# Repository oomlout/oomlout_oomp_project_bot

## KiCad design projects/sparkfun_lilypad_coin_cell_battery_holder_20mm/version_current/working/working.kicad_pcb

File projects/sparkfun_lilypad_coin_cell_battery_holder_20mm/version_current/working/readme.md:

# LilyPad_Coin_Cell_Battery_Holder-20mm by sparkfun  
This is a harvested standardized copy of a project from github.  
The original project can be found at:  
https://github.com/sparkfun/LilyPad_Coin_Cell_Battery_Holder-20mm  
Please consult that link for additional, details, files, and license information.  
Note: It was auto harvested and if the original repo had more than one board file or anything out of the ordinary the files here are likely not representative.

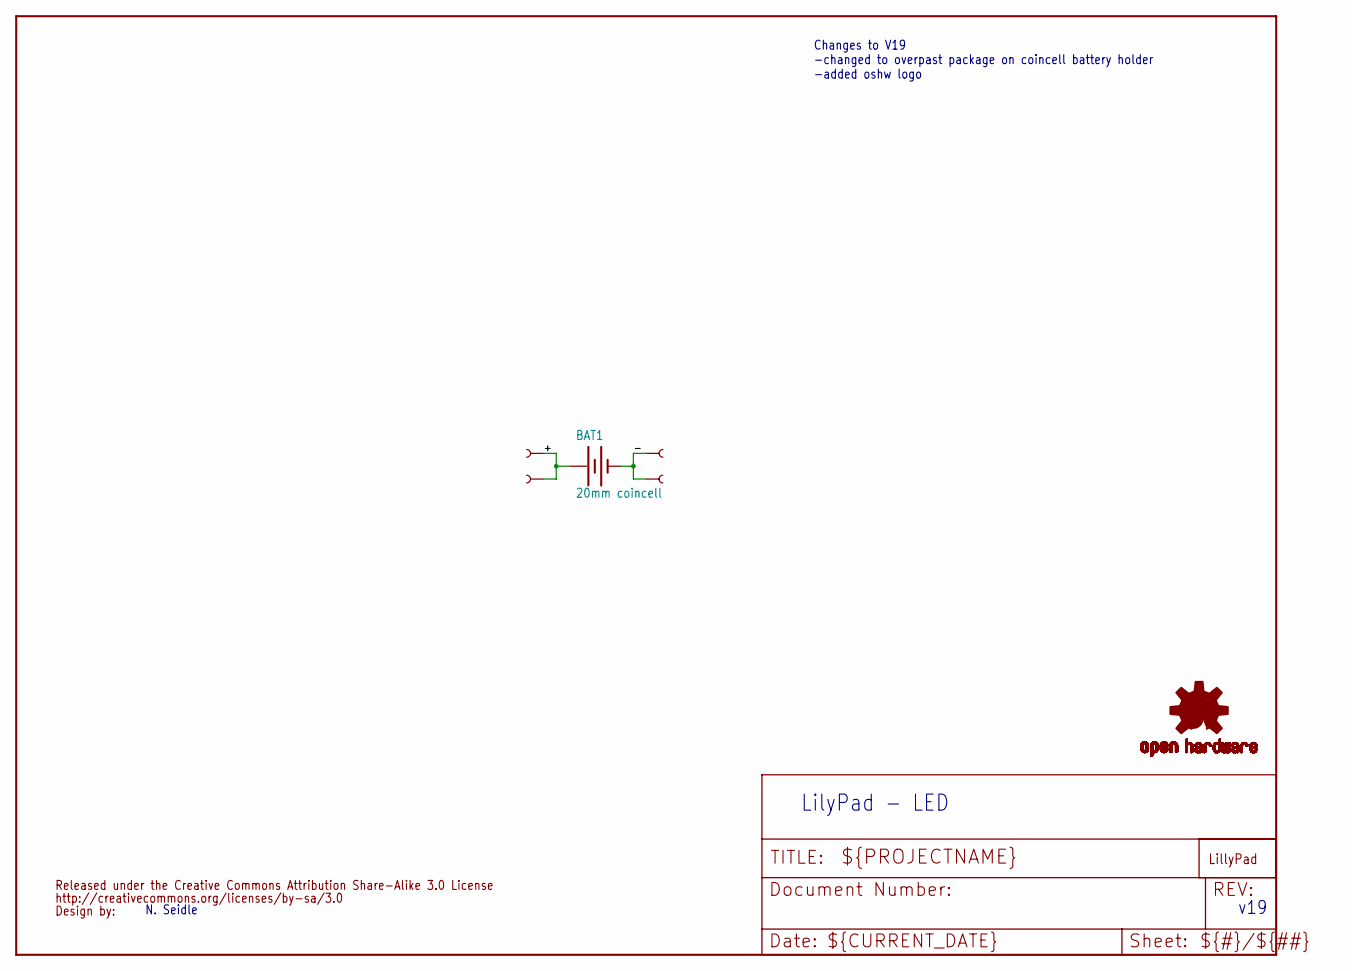
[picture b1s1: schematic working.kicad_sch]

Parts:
BAT1: 20mm coincell; BATTCON_20MM_4LEGS_OVERPASTE
U$1, U$2, U$3, U$4: SEWTAP6; PETAL-SMALL-2SIDE
U$5: LOGO-LPLP; LOGO-LILYPAD
U$6: CREATIVE_COMMONS
U$7: OSHW-LOGOS; OSHW-LOGO-S

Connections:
+: BAT1.1 (+), U$2.1, U$4.1
-: BAT1.2 (-), U$1.1, U$3.1

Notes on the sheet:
v19
Changes to V19 -changed to overpast package on coincell battery holder -added oshw logo
N. Seidle
LilyPad - LED

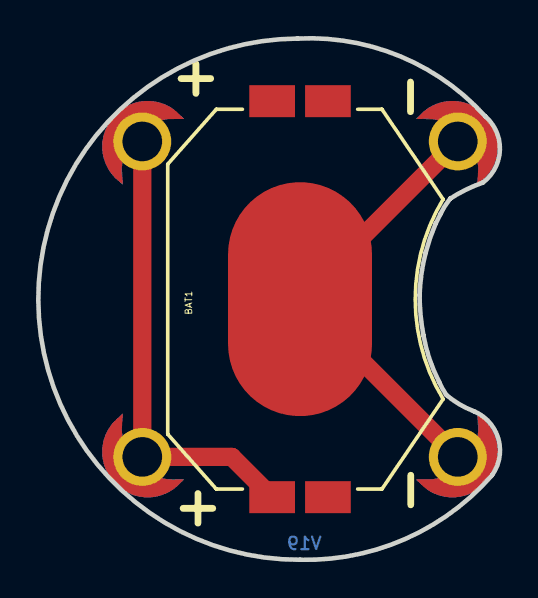
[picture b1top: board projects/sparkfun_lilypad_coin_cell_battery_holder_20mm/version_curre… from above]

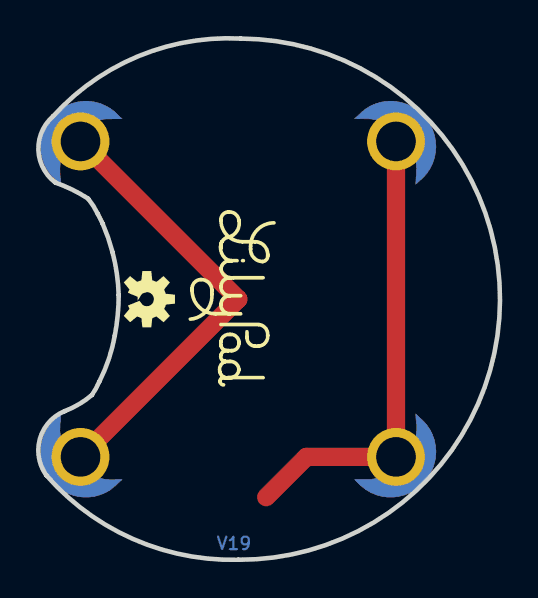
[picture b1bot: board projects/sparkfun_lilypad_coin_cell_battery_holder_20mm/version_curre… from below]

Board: 2 copper layers, 25.7 x 29.0 mm, 8 parts (2 on the bottom side), 2 nets.

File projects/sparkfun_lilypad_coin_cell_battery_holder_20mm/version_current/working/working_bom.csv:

Row,Description,Part,References,Value,Footprint,Quantity Per PCB,Status,Datasheet
1,,BATTERY20MM_4LEGS_OVERPASTE,BAT1,20mm coincell,BATTCON_20MM_4LEGS_OVERPASTE,1, ,
2,,CREATIVE_COMMONS,U$6,CREATIVE_COMMONS,CREATIVE_COMMONS,1, ,
3,,LOGO-LPLP,U$5,LOGO-LPLP,LOGO-LILYPAD,1, ,
4,,OSHW-LOGOS,U$7,OSHW-LOGOS,OSHW-LOGO-S,1, ,
5,,SEWTAP6,U$1 U$2 U$3 U$4,SEWTAP6,PETAL-SMALL-2SIDE,4, ,





Project info:
Schematic:,working
Variant:,default
Revision:,
Date:,2023-08-06_12-56-04
KiCad Version:,7.0.6-7.0.6~ubuntu22.04.1
Statistics:
Component Groups:,5
Component Count:,8 (0 SMD/ 0 THT)
Fitted Components:,8 (0 SMD/ 0 THT)
Number of PCBs:,1
Total Components:,8

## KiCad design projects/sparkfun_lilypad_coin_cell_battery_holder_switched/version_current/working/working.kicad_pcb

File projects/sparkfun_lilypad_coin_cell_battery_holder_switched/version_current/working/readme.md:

# OOMP Project  
## LilyPad_Coin_Cell_Battery_Holder-Switched  by sparkfun  
  
oomp key: oomp_projects_flat_sparkfun_lilypad_coin_cell_battery_holder_switched  
(snippet of original readme)  
  
SparkFun LilyPad Coin Cell Battery Holder-Switched  
========================================  

[*SparkFun LilyPad Coin Cell Battery Holder-Switched (DEV-11285)*](https://www.sparkfun.com/products/11285)  
  
This LilyPad Coin Cell Battery Holder has a small slide switch installed on the board,   
in-line with the power so you can shut off your project and save batteries.  
  
Repository Contents  
-------------------  
* **/Hardware** - All Eagle design files (.brd, .sch)  

License Information  
-------------------  
The hardware is released under [Creative Commons ShareAlike 4.0 International](https://creativecommons.org/licenses/by-sa/4.0/).  
Note: A portion of this sale is given back to Dr. Leah Buechley for continued development and education of e-textiles.  
  
Distributed as-is; no warranty is given.  
  
  full source readme at [readme_src.md](readme_src.md)  
  
source repo at: [https://github.com/sparkfun/LilyPad_Coin_Cell_Battery_Holder-Switched](https://github.com/sparkfun/LilyPad_Coin_Cell_Battery_Holder-Switched)  
## Board  

## Schematic  

[schematic pdf](working_schematic.pdf)  
## Images

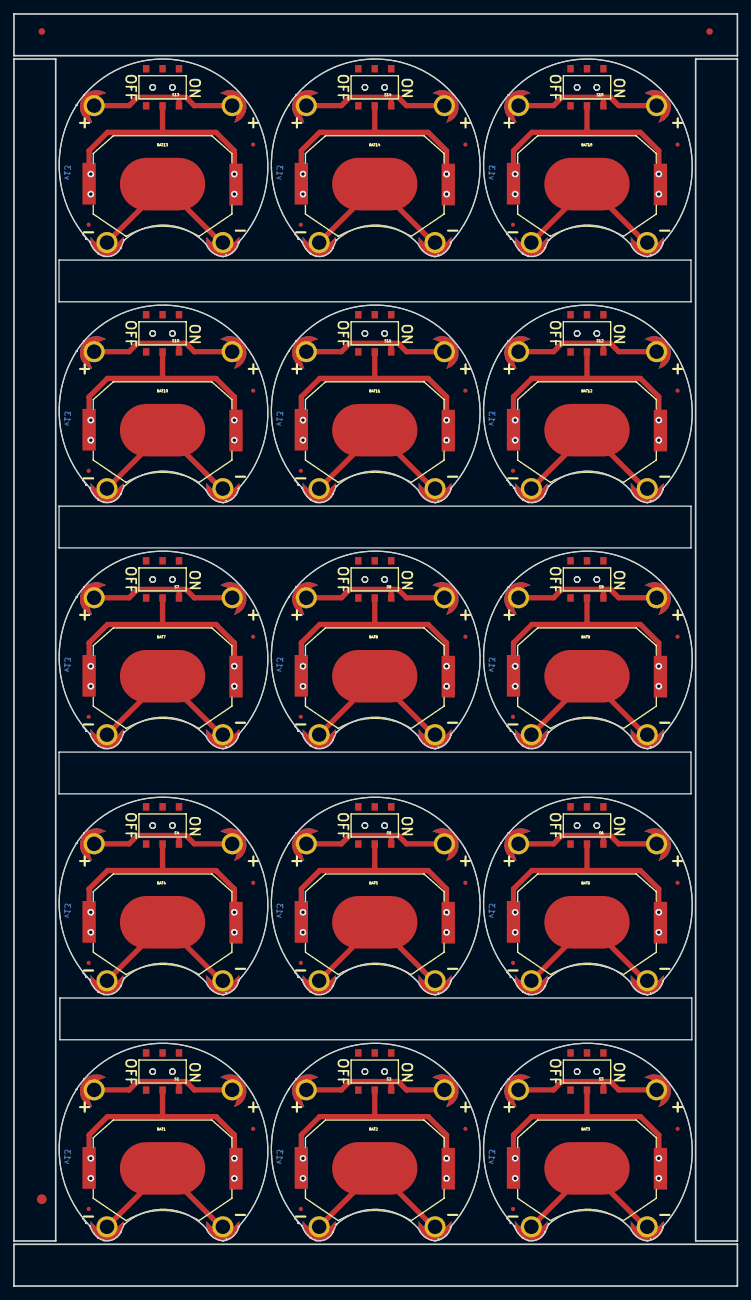
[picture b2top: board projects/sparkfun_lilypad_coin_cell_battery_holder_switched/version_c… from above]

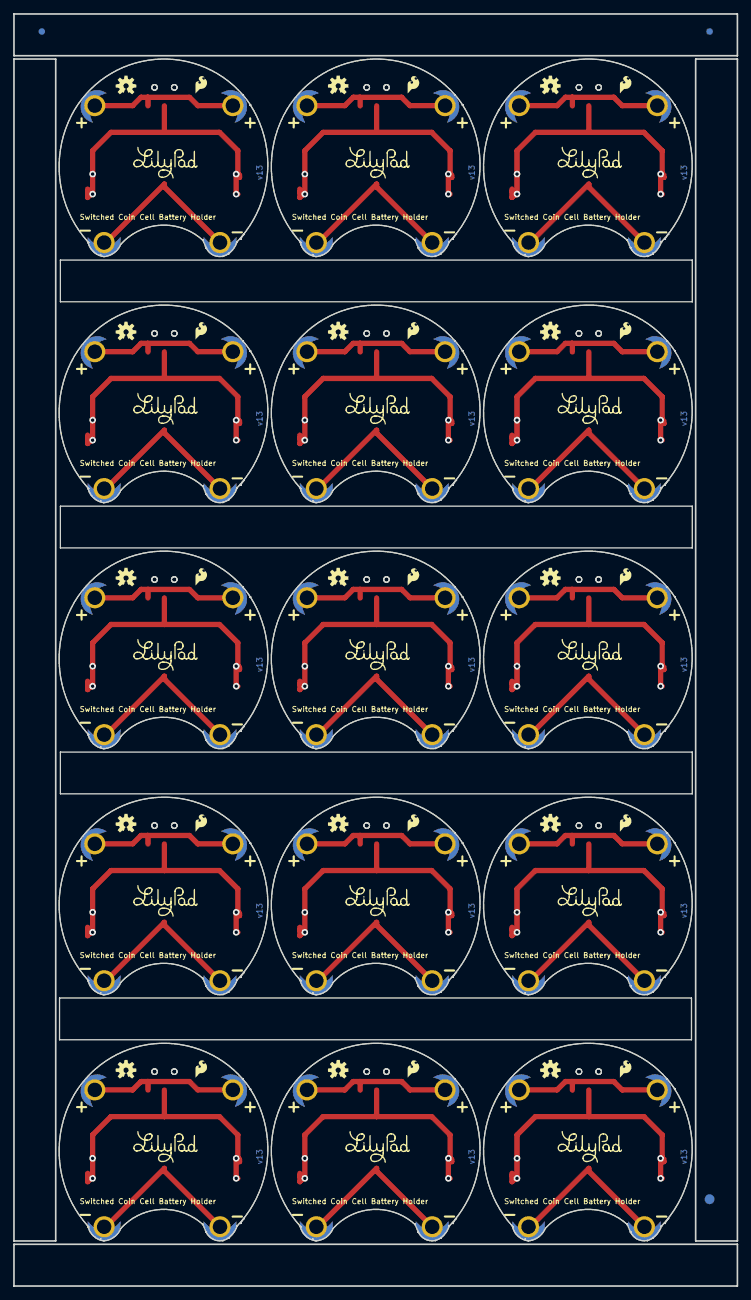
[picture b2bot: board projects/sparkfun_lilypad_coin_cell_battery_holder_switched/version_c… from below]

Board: 2 copper layers, 110.1 x 193.5 mm, 183 parts (48 on the bottom side), 45 nets.

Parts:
BAT1, BAT2, BAT3, BAT4, BAT5, BAT6, BAT7, BAT8, BAT9, BAT10, BAT11, BAT12, BAT13, BAT14, BAT15: 20mm coincell; BATTCON_20MM_4LEGS
BATB-0, BATB-1, BATB-2, BATB-3, BATB-4, BATB-5, BATB-6, BATB-7, BATB-8, BATB-9, BATB-10, BATB-11, BATB-12, BATB-13, BATB-14, BATB-15, BATB-16, BATB-17, BATB-18, BATB-19, BATB-20, BATB-21, BATB-22, BATB-23, BATB-24, BATB-25, BATB-26, BATB-27, BATB-28, BATB-29: SEWTAP6; PETAL-SMALL-2SIDE
BATT+0, BATT+1, BATT+2, BATT+3, BATT+4, BATT+5, BATT+6, BATT+7, BATT+8, BATT+9, BATT+10, BATT+11, BATT+12, BATT+13, BATT+14, BATT+15, BATT+16, BATT+17, BATT+18, BATT+19, BATT+20, BATT+21, BATT+22, BATT+23, BATT+24, BATT+25, BATT+26, BATT+27, BATT+28, BATT+29: SEWTAP6; PETAL-SMALL-2SIDE
E$1, E$2, E$3, E$4: FIDUCIAL-1X2
E$5, E$6: FIDUCIAL-1.5X3
FD1, FD2, FD3, FD4, FD5, FD6, FD7, FD8, FD9, FD10, FD11, FD12, FD13, FD14, FD15, FD16, FD17, FD18, FD19, FD20, FD21, FD22, FD23, FD24, FD25, FD26, FD27, FD28, FD29, FD30: FIDUCIALUFIDUCIAL; MICRO-FIDUCIAL
LOGO1, LOGO3, LOGO5, LOGO7, LOGO9, LOGO11, LOGO13, LOGO15, LOGO17, LOGO19, LOGO21, LOGO23, LOGO25, LOGO27, LOGO29: SFE_LOGO_FLAME.1_INCH; SFE_LOGO_FLAME_.1
LOGO2, LOGO4, LOGO6, LOGO8, LOGO10, LOGO12, LOGO14, LOGO16, LOGO18, LOGO20, LOGO22, LOGO24, LOGO26, LOGO28, LOGO30: OSHW-LOGOS; OSHW-LOGO-S
S1, S2, S3, S4, S5, S6, S7, S8, S9, S10, S11, S12, S13, S14, S15: AYZ0202
U$3, U$4, U$6, U$8, U$10, U$12, U$14, U$16, U$18, U$20, U$22, U$24, U$26, U$28, U$30: LOGO-LILYPAD
U$7, U$9, U$11, U$13, U$15, U$17, U$19, U$21, U$23, U$25, U$27, U$29: REVISION

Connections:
GND: BAT1.NEGATIVE, BATB-0.1, BATB-2.1
GND1: BAT2.NEGATIVE, BATB-1.1, BATB-3.1
GND2: BAT3.NEGATIVE, BATB-4.1, BATB-5.1
GND3: BAT4.NEGATIVE, BATB-6.1, BATB-7.1
GND4: BAT5.NEGATIVE, BATB-8.1, BATB-9.1
GND5: BAT6.NEGATIVE, BATB-10.1, BATB-11.1
GND6: BAT7.NEGATIVE, BATB-12.1, BATB-13.1
GND7: BAT8.NEGATIVE, BATB-14.1, BATB-15.1
GND8: BAT9.NEGATIVE, BATB-16.1, BATB-17.1
GND9: BAT10.NEGATIVE, BATB-18.1, BATB-19.1
GND10: BAT11.NEGATIVE, BATB-20.1, BATB-21.1
GND11: BAT12.NEGATIVE, BATB-22.1, BATB-23.1
GND12: BAT13.NEGATIVE, BATB-24.1, BATB-25.1
GND13: BAT14.NEGATIVE, BATB-26.1, BATB-27.1
GND14: BAT15.NEGATIVE, BATB-28.1, BATB-29.1
unnamed: BAT1.POSITIVE@1, BAT1.POSITIVE@2, BAT1.POSITIVE@3, BAT1.POSITIVE@4, S1.2
unnamed: BATT+0.1, BATT+2.1, S1.1
unnamed: BAT2.POSITIVE@1, BAT2.POSITIVE@2, BAT2.POSITIVE@3, BAT2.POSITIVE@4, S2.2
unnamed: BATT+1.1, BATT+3.1, S2.1
unnamed: BAT3.POSITIVE@1, BAT3.POSITIVE@2, BAT3.POSITIVE@3, BAT3.POSITIVE@4, S3.2
unnamed: BATT+4.1, BATT+5.1, S3.1
unnamed: BAT4.POSITIVE@1, BAT4.POSITIVE@2, BAT4.POSITIVE@3, BAT4.POSITIVE@4, S4.2
unnamed: BATT+6.1, BATT+7.1, S4.1
unnamed: BAT5.POSITIVE@1, BAT5.POSITIVE@2, BAT5.POSITIVE@3, BAT5.POSITIVE@4, S5.2
unnamed: BATT+8.1, BATT+9.1, S5.1
unnamed: BAT6.POSITIVE@1, BAT6.POSITIVE@2, BAT6.POSITIVE@3, BAT6.POSITIVE@4, S6.2
unnamed: BATT+10.1, BATT+11.1, S6.1
unnamed: BAT7.POSITIVE@1, BAT7.POSITIVE@2, BAT7.POSITIVE@3, BAT7.POSITIVE@4, S7.2
unnamed: BATT+12.1, BATT+13.1, S7.1
unnamed: BAT8.POSITIVE@1, BAT8.POSITIVE@2, BAT8.POSITIVE@3, BAT8.POSITIVE@4, S8.2
unnamed: BATT+14.1, BATT+15.1, S8.1
unnamed: BAT9.POSITIVE@1, BAT9.POSITIVE@2, BAT9.POSITIVE@3, BAT9.POSITIVE@4, S9.2
unnamed: BATT+16.1, BATT+17.1, S9.1
unnamed: BAT10.POSITIVE@1, BAT10.POSITIVE@2, BAT10.POSITIVE@3, BAT10.POSITIVE@4, S10.2
unnamed: BATT+18.1, BATT+19.1, S10.1
unnamed: BAT11.POSITIVE@1, BAT11.POSITIVE@2, BAT11.POSITIVE@3, BAT11.POSITIVE@4, S11.2
unnamed: BATT+20.1, BATT+21.1, S11.1
unnamed: BAT12.POSITIVE@1, BAT12.POSITIVE@2, BAT12.POSITIVE@3, BAT12.POSITIVE@4, S12.2
unnamed: BATT+22.1, BATT+23.1, S12.1
unnamed: BAT13.POSITIVE@1, BAT13.POSITIVE@2, BAT13.POSITIVE@3, BAT13.POSITIVE@4, S13.2
unnamed: BATT+24.1, BATT+25.1, S13.1
unnamed: BAT14.POSITIVE@1, BAT14.POSITIVE@2, BAT14.POSITIVE@3, BAT14.POSITIVE@4, S14.2
unnamed: BATT+26.1, BATT+27.1, S14.1
unnamed: BAT15.POSITIVE@1, BAT15.POSITIVE@2, BAT15.POSITIVE@3, BAT15.POSITIVE@4, S15.2
unnamed: BATT+28.1, BATT+29.1, S15.1

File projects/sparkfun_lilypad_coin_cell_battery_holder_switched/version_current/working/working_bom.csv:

"Id";"Designator";"Footprint";"Quantity";"Designation";"Supplier and ref";
1;"BATB-21,BATB-23,BATT+8,BATT+29,BATB-1,BATT+19,BATB-22,BATB-25,BATT+15,BATB-9,BATT+27,BATT+21,BATB-14,BATB-8,BATT+16,BATT+26,BATT+28,BATT+20,BATB-28,BATB-4,BATT+11,BATT+13,BATB-3,BATB-0,BATB-27,BATB-24,BATT+0,BATB-7,BATT+9,BATT+12,BATT+7,BATB-15,BATB-16,BATB-13,BATB-11,BATT+6,BATT+24,BATB-5,BATB-17,BATT+5,BATT+23,BATT+18,BATT+1,BATT+14,BATT+3,BATT+17,BATT+2,BATB-29,BATT+25,BATB-12,BATT+4,BATT+22,BATT+10,BATB-18,BATB-19,BATB-20,BATB-10,BATB-2,BATB-26,BATB-6";"PETAL-SMALL-2SIDE";60;"SEWTAP6";;;
2;"FD30,FD25,FD12,FD24,FD20,FD15,FD19,FD10,FD5,FD7,FD1,FD22,FD18,FD17,FD6,FD4,FD21,FD11,FD3,FD13,FD23,FD27,FD29,FD28,FD16,FD26,FD2,FD14,FD9,FD8";"MICRO-FIDUCIAL";30;"FIDUCIALUFIDUCIAL";;;
3;"U$17,U$11,U$13,U$21,U$15,U$9,U$27,U$7,U$19,U$25,U$29,U$23";"REVISION";12;"REVISION";;;
4;"S3,S12,S15,S5,S11,S4,S7,S6,S1,S8,S10,S14,S2,S9,S13";"AYZ0202";15;"";;;
5;"BAT5,BAT4,BAT9,BAT8,BAT2,BAT12,BAT6,BAT15,BAT14,BAT10,BAT11,BAT3,BAT7,BAT1,BAT13";"BATTCON_20MM_4LEGS";15;"20mm coincell";;;
6;"E$3,E$1,E$2,E$4";"FIDUCIAL-1X2";4;"";;;
7;"E$5,E$6";"FIDUCIAL-1.5X3";2;"";;;
8;"LOGO21,LOGO13,LOGO23,LOGO17,LOGO11,LOGO3,LOGO25,LOGO7,LOGO5,LOGO29,LOGO27,LOGO9,LOGO1,LOGO15,LOGO19";"SFE_LOGO_FLAME_.1";15;"SFE_LOGO_FLAME.1_INCH";;;
9;"LOGO14,LOGO16,LOGO8,LOGO20,LOGO26,LOGO6,LOGO10,LOGO24,LOGO30,LOGO22,LOGO18,LOGO12,LOGO2,LOGO28,LOGO4";"OSHW-LOGO-S";15;"OSHW-LOGOS";;;
10;"U$22,U$30,U$18,U$20,U$24,U$16,U$8,U$4,U$3,U$10,U$14,U$6,U$26,U$28,U$12";"LOGO-LILYPAD";15;"";;;

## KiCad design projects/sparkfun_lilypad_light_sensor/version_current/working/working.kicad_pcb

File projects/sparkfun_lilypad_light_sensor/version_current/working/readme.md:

# OOMP Project  
## LilyPad_Light_Sensor  by sparkfun  
  
oomp key: oomp_projects_flat_sparkfun_lilypad_light_sensor  
(snippet of original readme)  
  
LilyPad Light Sensor  
========================================  

[*LilyPad Light Sensor(DEV-08464)*](https://www.sparkfun.com/products/8464)  
  
This is a simple to use light sensor that outputs an analog value from 0 to 5V.   
With exposure to daylight, this sensor will output 5V.   
Covering the sensor with your hand, the sensor will output 0V.   
In a normal indoor lighting situation, the sensor will output from 1 to 2V.  
  
Repository Contents  
-------------------  
* **/Firmware** - Arduino Example Code  
* **/Hardware** - Eagle design files (.brd, .sch)  
* **/Production** - Production panel files (.brd)  
  
Documentation  
--------------  
* **[Hookup Guide](https://learn.sparkfun.com/tutorials/lilypad-light-sensor-hookup-guide)** - Basic hookup guide for the LilyPad Light Sensor.  
* **[SparkFun Fritzing repo](https://github.com/sparkfun/Fritzing_Parts)** - Fritzing diagrams for SparkFun products.  
* **[SparkFun 3D Model repo](https://github.com/sparkfun/3D_Models)** - 3D models of SparkFun products.   

License Information  
-------------------  
This product is _**open source**_!   
  
The **hardware** is released under [Creative Commons ShareAlike 4.0 International](https://creativecommons.org/licenses/by-sa/4.0/).  
  
Please use, reuse, and modify these files as you see fit. Please maintain attribution to SparkFun Electronics and release anything derivative under the same license.  
  
Distributed as-is; no warranty is given.  
  full source readme at [readme_src.md](readme_src.md)  
  
source repo at: [https://github.com/sparkfun/LilyPad_Light_Sensor](https://github.com/sparkfun/LilyPad_Light_Sensor)  
## Board  

## Schematic  

[schematic pdf](working_schematic.pdf)  
## Images

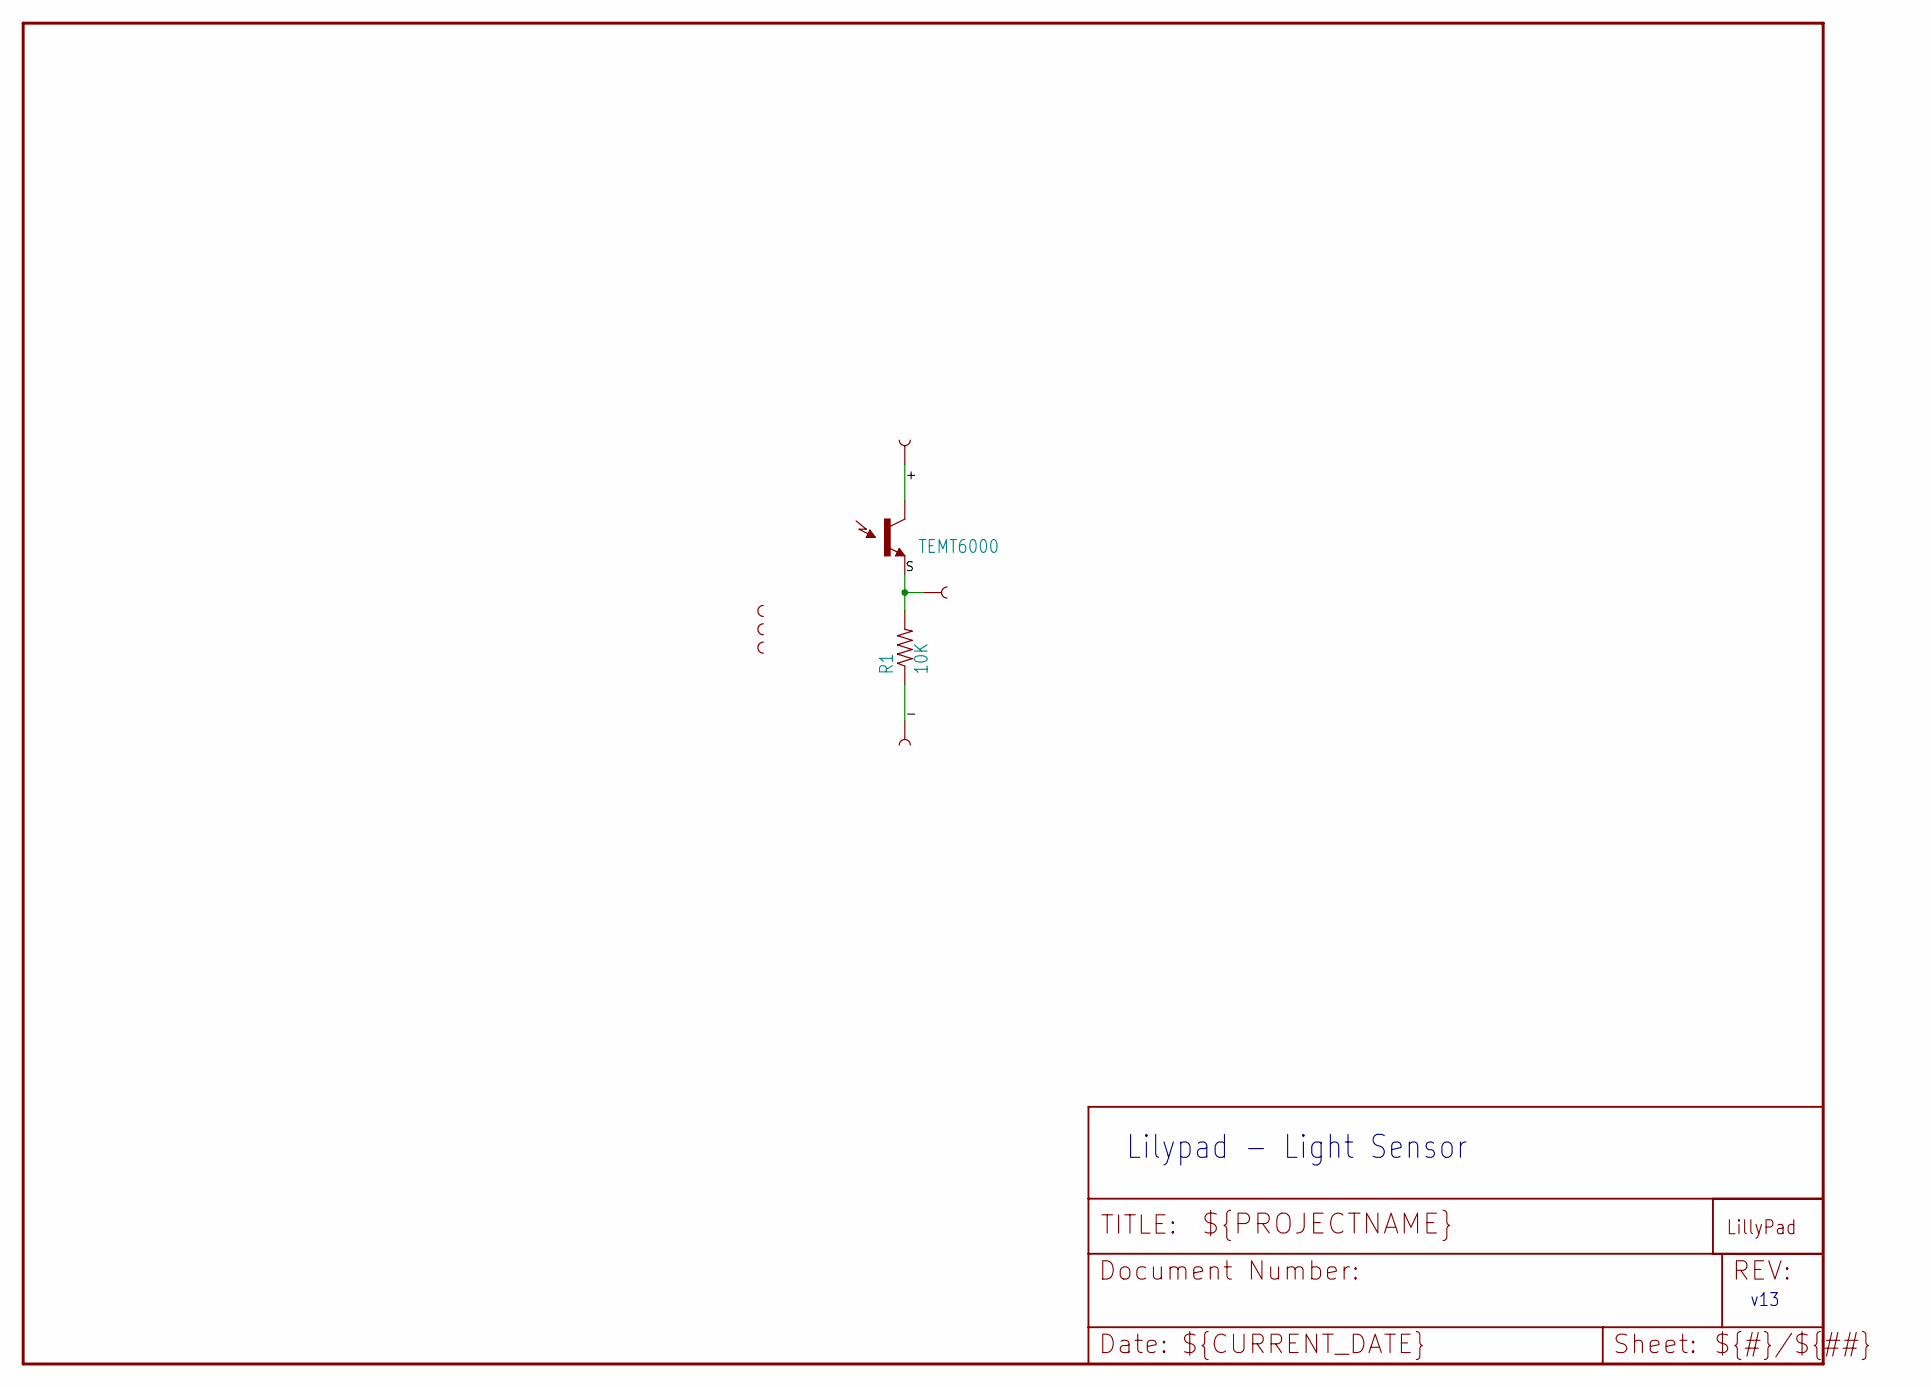
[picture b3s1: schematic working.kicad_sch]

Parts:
LIGHT1, LIGHT2, LIGHT3: SEWTAP-NOHOLE2; PETAL-NOHOLE-2SIDE
LIGHT+0: SEWTAP6; PETAL-SMALL-2SIDE
LIGHT-0: SEWTAP6; PETAL-SMALL-2SIDE
LIGHTS0: SEWTAP6; PETAL-SMALL-2SIDE
R1: 10K; C0402
U1: TEMT6000; TEMT6000-SEN
U$2: LOGO-LPLP; LOGO-LILYPAD

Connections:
+: LIGHT+0.1, U1.COLLECTOR (C1)
-: LIGHT-0.1, R1.1
S: LIGHTS0.1, R1.2, U1.EMITTER (E1)

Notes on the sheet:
v13
Lilypad - Light Sensor

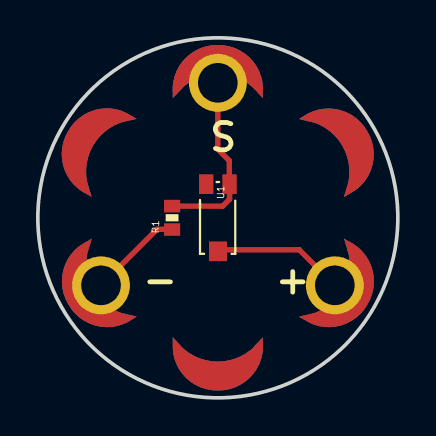
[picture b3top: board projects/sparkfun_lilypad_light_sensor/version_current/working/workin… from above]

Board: 2 copper layers, 20.0 x 20.0 mm, 9 parts (1 on the bottom side), 3 nets.

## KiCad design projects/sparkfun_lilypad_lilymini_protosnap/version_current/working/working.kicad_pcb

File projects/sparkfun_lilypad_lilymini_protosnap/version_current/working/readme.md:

# LilyPad_LilyMini_ProtoSnap by sparkfun  
This is a harvested standardized copy of a project from github.  
The original project can be found at:  
https://github.com/sparkfun/LilyPad_LilyMini_ProtoSnap  
Please consult that link for additional, details, files, and license information.  
Note: It was auto harvested and if the original repo had more than one board file or anything out of the ordinary the files here are likely not representative.

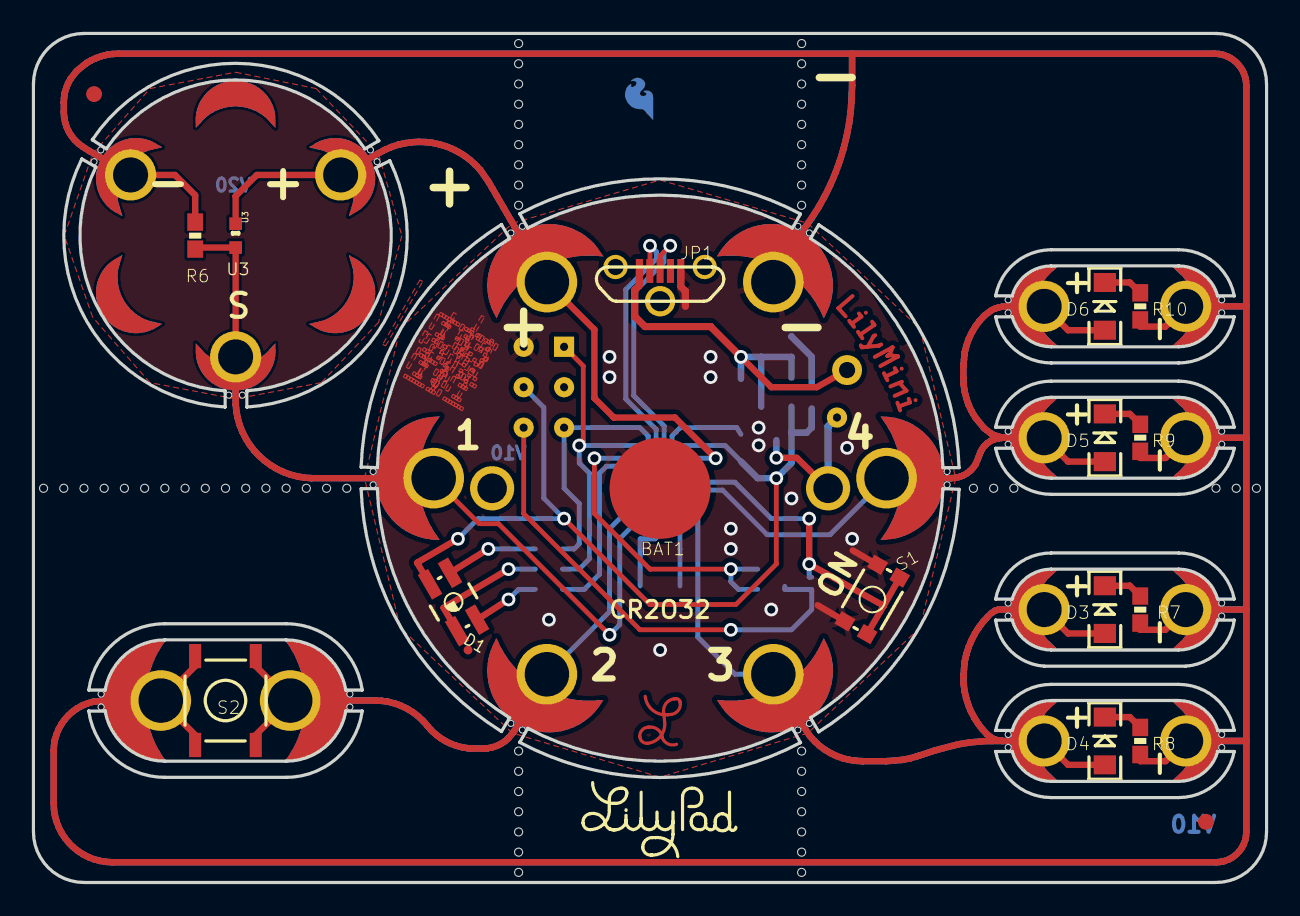
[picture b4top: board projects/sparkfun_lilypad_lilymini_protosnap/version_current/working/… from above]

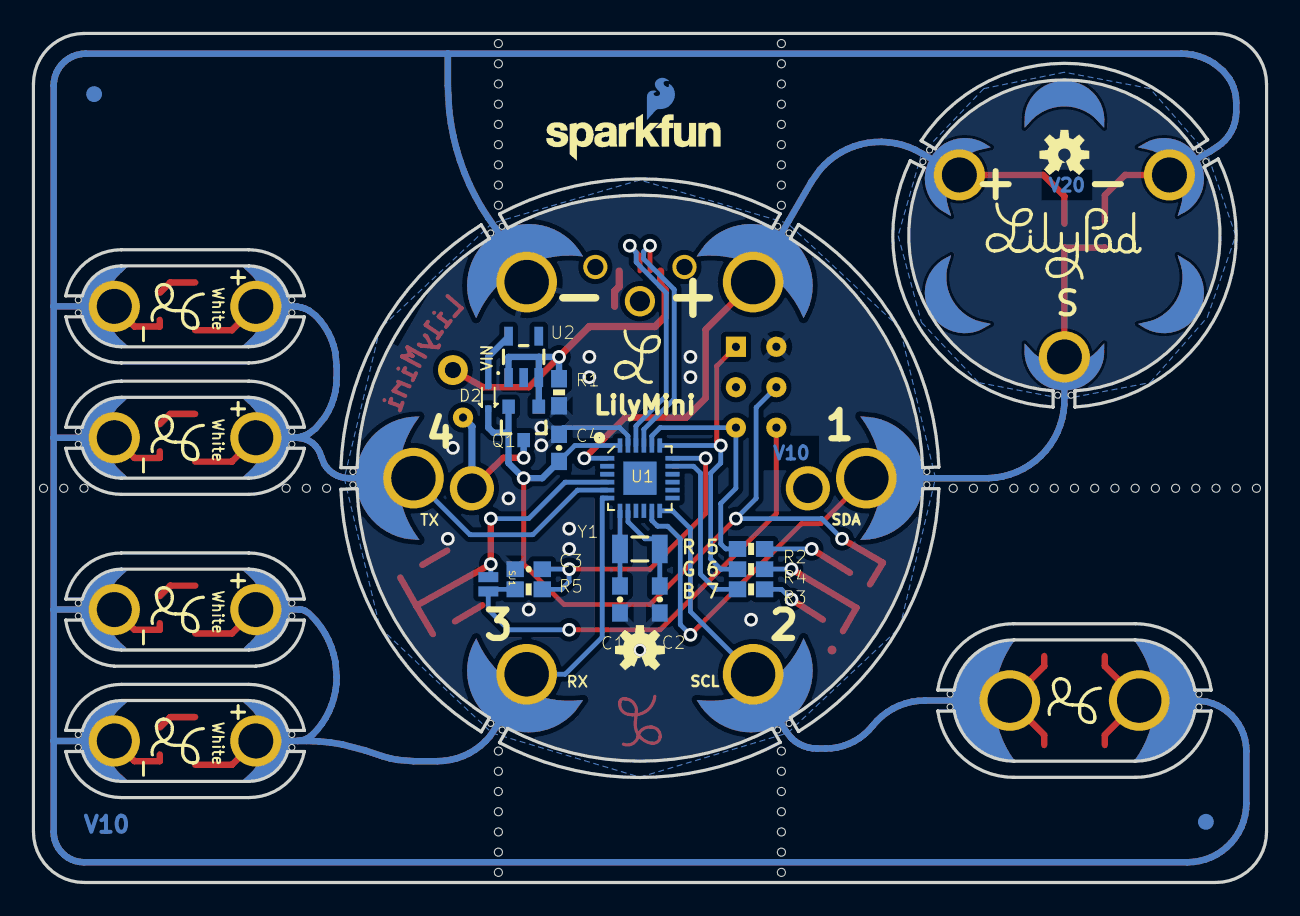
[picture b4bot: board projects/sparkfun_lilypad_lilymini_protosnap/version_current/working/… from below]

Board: 2 copper layers, 77.5 x 53.3 mm, 170 parts (35 on the bottom side), 27 nets.

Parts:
$1_61_$_2016-09-25_21-56-09: OSHW-LOGOS; OSHW-LOGO-S
@HOLE0, @HOLE1, @HOLE2, @HOLE3, @HOLE4, @HOLE5, @HOLE6, @HOLE7, @HOLE8, @HOLE9, @HOLE10, @HOLE11, @HOLE12, @HOLE13, @HOLE14, @HOLE15, @HOLE16, @HOLE17, @HOLE18, @HOLE19, @HOLE20, @HOLE21, @HOLE22, @HOLE23, @HOLE24, @HOLE25, @HOLE26, @HOLE27, @HOLE28, @HOLE29, @HOLE30, @HOLE31, @HOLE32, @HOLE33, @HOLE34, @HOLE35, @HOLE36, @HOLE37, @HOLE38, @HOLE39, @HOLE40, @HOLE41, @HOLE42, @HOLE43, @HOLE44, @HOLE45, @HOLE46, @HOLE47, @HOLE48, @HOLE49, @HOLE50, @HOLE51, @HOLE52, @HOLE53, @HOLE54, @HOLE55, @HOLE56, @HOLE57, @HOLE58, @HOLE59, @HOLE60, @HOLE61, @HOLE62, @HOLE63, @HOLE64, @HOLE65, @HOLE66, @HOLE67, @HOLE68, @HOLE69, @HOLE70, @HOLE71, @HOLE72, @HOLE73, @HOLE74, @HOLE75, @HOLE76, @HOLE77, @HOLE78, @HOLE79, @HOLE80, @HOLE81, @HOLE82, @HOLE83, @HOLE84, @HOLE85, @HOLE86, @HOLE87, @HOLE88, @HOLE89, @HOLE90, @HOLE91: (no value)
BAT1: CR2032; BATTERY_20MM_PTH_KIT
C1, C2: 15pF; 0603-CAP
C3, C4: 0.1uF; 0603-CAP
D1: P-LCC-4-3
D2: RB751; SOD-523
D3, D4, D5, D6: LED-1206
FD1, FD2, FD3, FD4: FIDUCIAL1X2; FIDUCIAL-1X2
FRAME1: FRAME-LETTER; CREATIVE_COMMONS
JP1: USB-B-MICRO-SMD_VERT
JP2: 1X01NS
JP3: 1X01_POGOPIN_PAD_NOSILK_1SIDE_SQUARE
JP4, JP5, JP6, JP7, JP8, JP9: 1X01_POGOPIN_PAD_NOSILK_1SIDE_ROUND
JP12, JP13: PETAL-MEDIUM-2SIDE
JP20, JP21, JP22, JP23, JP24, JP25, JP26, JP27: PETAL-SMALL-2SIDE
LOGO1: LOGO-L
LOGO2: LOGO-L-TOP
LOGO3: OSHW-LOGOS; OSHW-LOGO-S
LOGO4: SFE_LOGO_NAME.1_INCH; SFE_LOGO_NAME_.1
Q1: ZXMP6A13F; SOT23-3
R1, R6: 10K; 0603-RES
R2, R5: 330; 0603-RES
R3: 2K; 0603-RES
R4: 1K; 0603-RES
R7, R8, R9, R10: 150; 0603-RES
S1: TACTILE_SWITCH_SMD_4.6X2.8MM
S2: TACTILE-SWITCH-SMD
SEWTAP1, SEWTAP2, SEWTAP3, SEWTAP4: PETAL-MEDIUM-2SIDE
SEWTAP+0: PETAL-MEDIUM-2SIDE
SEWTAP-0: PETAL-MEDIUM-2SIDE
SEWTAPLS+0: PLUS; PETAL-SMALL-2SIDE
SEWTAPLS-0: MINUS; PETAL-SMALL-2SIDE
SEWTAPLSOUT0: OUT; PETAL-SMALL-2SIDE
SJ1: PAD-JUMPER-2-NO_NO_SILK
ST1, ST2, ST3: PETAL-NOHOLE-2SIDE
U1: SAMD11D14A-M; QFN-24_ALT2
U2: AP2112K-3.3V; SOT23-5
U3: ALS-PT19
U$1: LOGO-LILYPAD
U$2: LOGO-LPLP; LOGO-LILYPAD
U$4: SFE_LOGO_FLAME_COPPER_EXPOSED_.1
U$5, U$6, U$7, U$8, U$9: LOGO-L
Y1: 32.768kHz; CRYSTAL-SMD-3.2X1.5MM

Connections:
B: D1.3, R2.2
BATT3V: BAT1.+1, BAT1.+2, JP9.P$1, Q1.3
BUTTON: S1.1, S1.2, SJ1.1, U1.4
G: D1.2, R3.2
GND: BAT1.-3, C1.1, C2.1, C3.2, C4.2, JP1.GND, JP4.P$1, JP13.1, JP21.1, JP23.1, JP25.1, JP27.1, R1.1, R6.1, R7.1, R8.1, R9.1, R10.1, S1.3, S1.4, S2.3, S2.4, SEWTAP-0.1, SEWTAPLS-0.1, U1.23, U2.2
unnamed: D2.A, U2.5
unnamed: D3.C, R7.2
unnamed: D4.C, R8.2
unnamed: D5.C, R9.2
unnamed: D6.C, R10.2
R: D1.1, R4.2
SEWTAP1: R6.2, SEWTAP1.1, SEWTAPLSOUT0.1, U1.11, U3.E
SEWTAP2: JP12.1, S2.1, S2.2, SEWTAP2.1, U1.12
SEWTAP3: D3.A, D4.A, JP20.1, JP22.1, SEWTAP3.1, U1.6
SEWTAP4: D5.A, D6.A, JP24.1, JP26.1, SEWTAP4.1, U1.5
SEWTAP+: SEWTAP+0.1, SEWTAPLS+0.1, U1.1, U3.C
USB5V: JP1.VBUS, JP2.1, Q1.1, R1.2, U2.1, U2.3
USB_N: JP1.D-, U1.21
USB_P: JP1.D+, U1.22
VDD: C4.1, D1.4, D2.C, JP6.P$1, Q1.2, U1.24
X1: C1.2, U1.7, Y1.P$2
X2: C2.2, U1.8, Y1.P$1
~BLUE/SWDIO: JP7.P$1, R2.1, U1.20
~GREEN: R3.1, U1.17
~RED/SWDCLK: JP3.P$1, R4.1, U1.19
~RST: JP8.P$1, R5.2, SJ1.2
~RST1: C3.1, R5.1, U1.18

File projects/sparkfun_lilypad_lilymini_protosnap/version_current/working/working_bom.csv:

Row,Description,Part,References,Value,Footprint,Quantity Per PCB,Status,Datasheet
1,,OSHW-LOGOS,$1_61_$_2016-09-25_21-56-09,OSHW-LOGOS,OSHW-LOGO-S,1, ,
2,,BATTERY20MM_PTH_KIT,BAT1,CR2032,BATTERY_20MM_PTH_KIT,1, ,
3,,15PF-50V-5%(0603),C1 C2,15pF,0603-CAP,2, ,
4,,0.1UF-25V(+80/-20%)(0603),C3 C4,0.1uF,0603-CAP,2, ,
5,,0.13_RGB_LEDPLCC,D1,0.13_RGB_LEDPLCC,P-LCC-4-3,1, ,
6,,DIODE-SCHOTTKY-RB751,D2,DIODE-SCHOTTKY-RB751,SOD-523,1, ,
7,,LED-WHITE1206,D3 D4 D5 D6,LED-WHITE1206,LED-1206,4, ,
8,,FRAME-LETTER,FRAME1,FRAME-LETTER,CREATIVE_COMMONS,1, ,
9,,SparkFun-Connectors_M01SMDNS,JP2,M01SMDNS,1X01NS,1, ,
10,,M01_POGOPAD_20M_NS_1S_ROUND,JP4 JP5 JP6 JP7 JP8 JP9,M01_POGOPAD_20M_NS_1S_ROUND,1X01_POGOPIN_PAD_NOSILK_1SIDE_ROUND,6, ,
11,,M01_POGOPAD_20M_NS_1S_SQUARE,JP3,M01_POGOPAD_20M_NS_1S_SQUARE,1X01_POGOPIN_PAD_NOSILK_1SIDE_SQUARE,1, ,
12,,SEWTAP6,JP20 JP21 JP22 JP23 JP24 JP25 JP26 JP27 SEWTAPLS+0 SEWTAPLS-0 SEWTAPLSOUT0,SEWTAP6,PETAL-SMALL-2SIDE,11, ,
13,,SEWTAP8,JP12 JP13 SEWTAP1 SEWTAP2 SEWTAP3 SEWTAP4 SEWTAP+0 SEWTAP-0,SEWTAP8,PETAL-MEDIUM-2SIDE,8, ,
14,,USB_MICROB_PLUGUSB-B-MICRO-SMD-VERT,JP1,USB_MICROB_PLUGUSB-B-MICRO-SMD-VERT,USB-B-MICRO-SMD_VERT,1, ,
15,,LILYLOGO-L-TOP,LOGO2,LILYLOGO-L-TOP,LOGO-L-TOP,1, ,
16,,LOGO-LPL,LOGO1,LOGO-LPL,LOGO-L,1, ,
17,,SFE_LOGO_NAME.1_INCH,LOGO4,SFE_LOGO_NAME.1_INCH,SFE_LOGO_NAME_.1,1, ,
18,,MOSFET-PCHANNEL,Q1,MOSFET-PCHANNEL,SOT23-3,1, ,
19,,RESISTOR0603,R7 R8 R9 R10,150,0603-RES,4, ,
20,,330OHM1/10W1%(0603),R2 R5,330,0603-RES,2, ,
21,,1KOHM-1/10W-1%(0603),R4,1K,0603-RES,1, ,
22,,2.0KOHM1/10W5%(0603),R3,2K,0603-RES,1, ,
23,,10KOHM-1/10W-1%(0603)0603,R1 R6,10K,0603-RES,2, ,
24,,SWITCH-MOMENTARY-2SMD-4.6X2.8MM,S1,SWITCH-MOMENTARY-2SMD-4.6X2.8MM,TACTILE_SWITCH_SMD_4.6X2.8MM,1, ,
25,,SWITCH-MOMENTARY-2SMD-REDUNDANT,S2,SWITCH-MOMENTARY-2SMD-REDUNDANT,TACTILE-SWITCH-SMD,1, ,
26,,JUMPER-PAD-2-NO,SJ1,JUMPER-PAD-2-NO,PAD-JUMPER-2-NO_NO_SILK,1, ,
27,,SEWTAP-NOHOLE2,ST1 ST2 ST3,SEWTAP-NOHOLE2,PETAL-NOHOLE-2SIDE,3, ,
28,,LIGHTSENSORALS,U3,LIGHTSENSORALS,ALS-PT19,1, ,
29,,SAMD11D14A-M,U1,SAMD11D14A-M,QFN-24_ALT2,1, ,
30,,V_REG_AP2112K-3.3V,U2,V_REG_AP2112K-3.3V,SOT23-5,1, ,
31,,CRYSTAL3.2X1.5MM,Y1,32.768kHz,CRYSTAL-SMD-3.2X1.5MM,1, ,





Project info:
Schematic:,working
Variant:,default
Revision:,
Date:,2023-08-06_12-56-04
KiCad Version:,7.0.6-7.0.6~ubuntu22.04.1
Statistics:
Component Groups:,31
Component Count:,65 (0 SMD/ 0 THT)
Fitted Components:,65 (0 SMD/ 0 THT)
Number of PCBs:,1
Total Components:,65

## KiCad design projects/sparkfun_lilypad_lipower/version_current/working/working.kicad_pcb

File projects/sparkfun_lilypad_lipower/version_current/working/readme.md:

# LilyPad_LiPower by sparkfun  
This is a harvested standardized copy of a project from github.  
The original project can be found at:  
https://github.com/sparkfun/LilyPad_LiPower  
Please consult that link for additional, details, files, and license information.  
Note: It was auto harvested and if the original repo had more than one board file or anything out of the ordinary the files here are likely not representative.

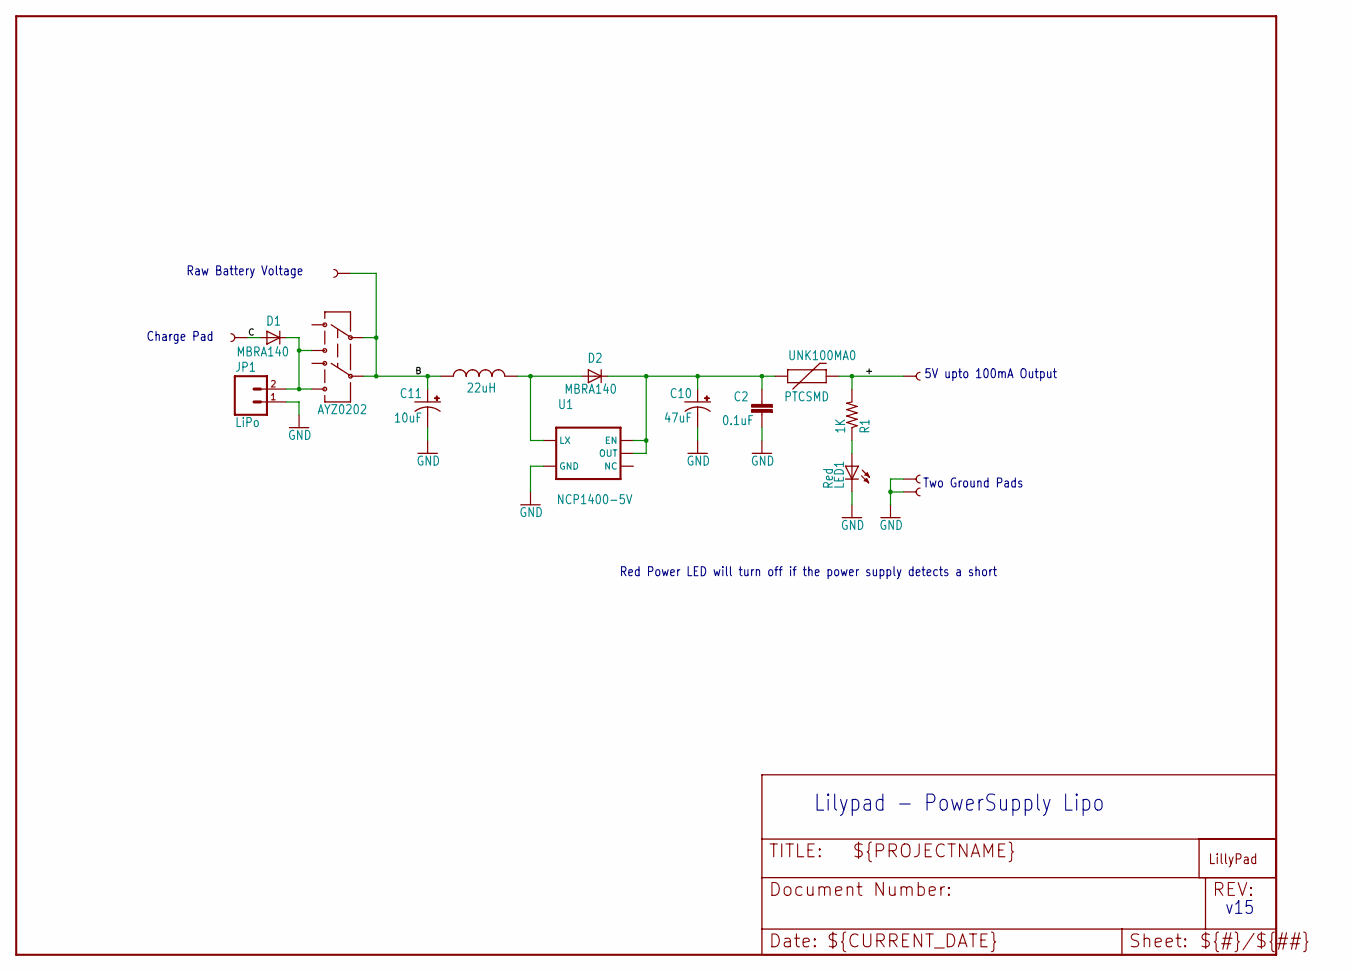
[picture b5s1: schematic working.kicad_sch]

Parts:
C2: 0.1uF; 0603-CAP
C10: 47uF; EIA3528-21
C11: 10uF; CPOL_1206
D1, D2: MBRA140; SMA-DIODE
JP1: LiPo; JST-2-SMD
L1: 22uH; CR54
LED1: Red; LED-1206
R1: 1K; 0603-RES
S1: AYZ0202
U1: NCP1400-5V; SOT23-5
U$1, U$2, U$3, U$4, U$5: SEWTAP10; PETAL-LONG-2-2SIDE
U$7: LOGO-LPLP; LOGO-LILYPAD
UNK100MA0: PTCSMD; PTC-1206

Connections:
+: R1.2, U$1.1, UNK100MA0.2
B: C11.A (+), L1.P$2 (2), S1.2, S1.5, U$3.1
C: D1.A, U$2.1
GND: C2.2, C10.C (-), C11.C (-), JP1.1, LED1.C, U1.4 (GND), U$4.1, U$5.1
unnamed: LED1.A, R1.1
unnamed: C2.1, C10.A (+), D2.C, U1.1 (EN), U1.2 (OUT), UNK100MA0.1
unnamed: D1.C, JP1.2, S1.1 (3), S1.4 (6)
unnamed: D2.A, L1.P$1 (1), U1.5 (LX)

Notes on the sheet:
Two Ground Pads
Raw Battery Voltage
5V upto 100mA Output
Lilypad - PowerSupply Lipo
Red Power LED will turn off if the power supply detects a short
v15
Charge Pad

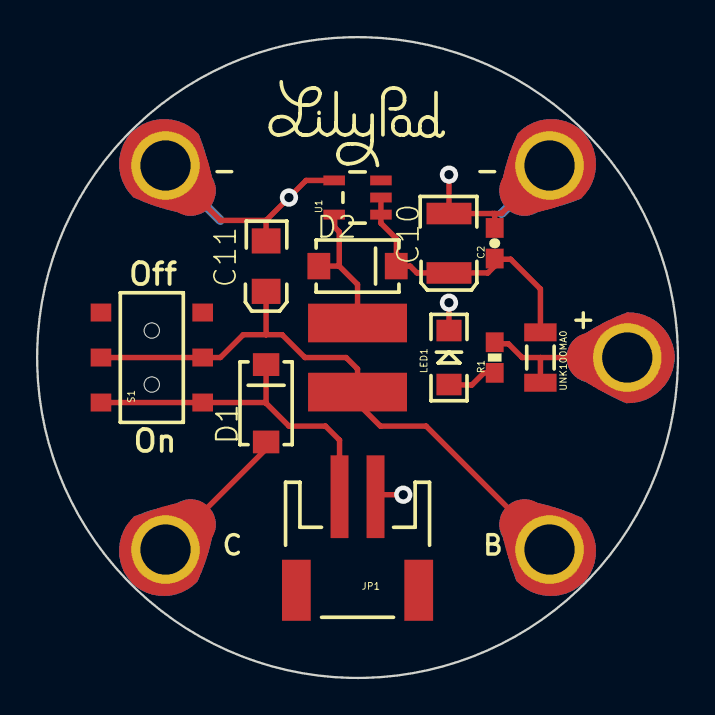
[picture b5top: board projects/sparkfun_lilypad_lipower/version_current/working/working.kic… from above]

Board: 2 copper layers, 35.6 x 35.6 mm, 18 parts (0 on the bottom side), 8 nets.

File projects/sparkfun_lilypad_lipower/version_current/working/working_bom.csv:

Row,Description,Part,References,Value,Footprint,Quantity Per PCB,Status,Datasheet
1,,CAP0603-CAP,C2,0.1uF,0603-CAP,1, ,
2,,CAP_POL1206,C11,10uF,CPOL_1206,1, ,
3,,CAP_POL2,C10,47uF,EIA3528-21,1, ,
4,,DIODESMA,D1 D2,MBRA140,SMA-DIODE,2, ,
5,,M02-JST-2MM-SMT,JP1,LiPo,JST-2-SMD,1, ,
6,,INDUCTORCR54,L1,22uH,CR54,1, ,
7,,LED1206,LED1,Red,LED-1206,1, ,
8,,RESISTOR0603-RES,R1,1K,0603-RES,1, ,
9,,AYZ0202,S1,AYZ0202,AYZ0202,1, ,
10,,V_REG_NCP1400SOT23-5,U1,NCP1400-5V,SOT23-5,1, ,
11,,LOGO-LPLP,U$7,LOGO-LPLP,LOGO-LILYPAD,1, ,
12,,SEWTAP10,U$1 U$2 U$3 U$4 U$5,SEWTAP10,PETAL-LONG-2-2SIDE,5, ,
13,,PTCSMD,UNK100MA0,PTCSMD,PTC-1206,1, ,





Project info:
Schematic:,working
Variant:,default
Revision:,
Date:,2023-08-06_12-56-04
KiCad Version:,7.0.6-7.0.6~ubuntu22.04.1
Statistics:
Component Groups:,13
Component Count:,18 (0 SMD/ 0 THT)
Fitted Components:,18 (0 SMD/ 0 THT)
Number of PCBs:,1
Total Components:,18

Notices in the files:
projects/sparkfun_lilypad_coin_cell_battery_holder_20mm/version_current/working/working.kicad_sch:
http://creativecommons.org/licenses/by-sa/3.0
Released under the Creative Commons Attribution Share-Alike 3.0 License
parts and their libraries:
Released under the Creative Commons Attribution Share-Alike 4.0 License
